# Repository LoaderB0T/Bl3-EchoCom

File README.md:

# Borderlands 3 - Echo Device

This repo contains all the needed files to create your own 3D printed Echo Com from Borderlands 3.
I put lots of images in the repo so the size got quite big, sorry for that 🤷‍♂️.

If you need additional information or have any questions please just open an issue and I will try to answer them 😀.
And please, if you decide to give it a shot and you use my model, please please send me pictures of the result! :) Just open an issue here to show off your amazing work.

## Printing

- I printed all opaque parts with PLA filament with 0.15mm layer height.
- For the electronics version, the inner projector part was printed with "transparent" PETG filament to let the light of the LEDs pass through.
- I Recommend printing more or less everything with full support to make sure all the complex parts get printed properly.
- Removing the supports is quite easy with this model.

## Components for the electronics version

- [4" TFT Display](https://www.waveshare.com/4inch-tft-touch-shield.htm)
  - I really recommend buying exactly this one as the 3D model is designed for exactly this product.
  - It was the only display I found that had the correct size for the EchoCom.
  - You have to remove the pin headers from the backside for it to fit into the model. The required wires then can be re-soldered with a thinner footprint.
- Custom PCB
  - You can find the KiCad project and a finished plot of the PCB in the `pcb` folder.
  - Use a service like [JLCPCB](jlcpcb.com) to have it manufactured or you can of course do it yourself :)
- Electronic Components:
  - 1x Atmega328P-PU
  - 8x Push Button
  - 2x 22pF ceramic capacitors
  - 1x 16MHz Crystal
  - 3x 100nF foil capacitor
  - 1x 10K Ohm resistor
  - 2x Digital RGB LEDs (eg WS2812B) (one or maybe more than two might also work for you)
  - 2x Screw Terminals (optional, you can also solder the power wires)
  - Pin Header (optional, you can also solder the wires, but I recommend the headers!)
    - 2x 3-pin
    - 2x 5-pin
    - 1x 6-pin
- Some sort of power source (I have not yet figured this out)
- Wires (with correct heads depending on your pin headers)

## Code

The code is very, very unfinished!
I recommend [Visual Studio Code](https://code.visualstudio.com/) to edit the code. The code is a [PlatformIO](https://platformio.org/) project, so I recommend the [PlatformIO extension](https://marketplace.visualstudio.com/items?itemName=platformio.platformio-ide) for VSCode.

## Images

|                                                                                                                  |                                                                                                                   |                                                                                                                   |
| :--------------------------------------------------------------------------------------------------------------: | :---------------------------------------------------------------------------------------------------------------: | :---------------------------------------------------------------------------------------------------------------: |
|  |   |   |
|  |   |   |
|  |  |  |

## Progress images

|                                                                                                                                       |                                                                                                                                       |                                                                                                                                       |
| :-----------------------------------------------------------------------------------------------------------------------------------: | :-----------------------------------------------------------------------------------------------------------------------------------: | :-----------------------------------------------------------------------------------------------------------------------------------: |
|  |  |  |
|  |  |  |
|  |  |  |
|  |  |  |
|  |  |  |
|  |  |  |
|  |  |  |
|  |  |  |
|  |  |  |
|  |  |

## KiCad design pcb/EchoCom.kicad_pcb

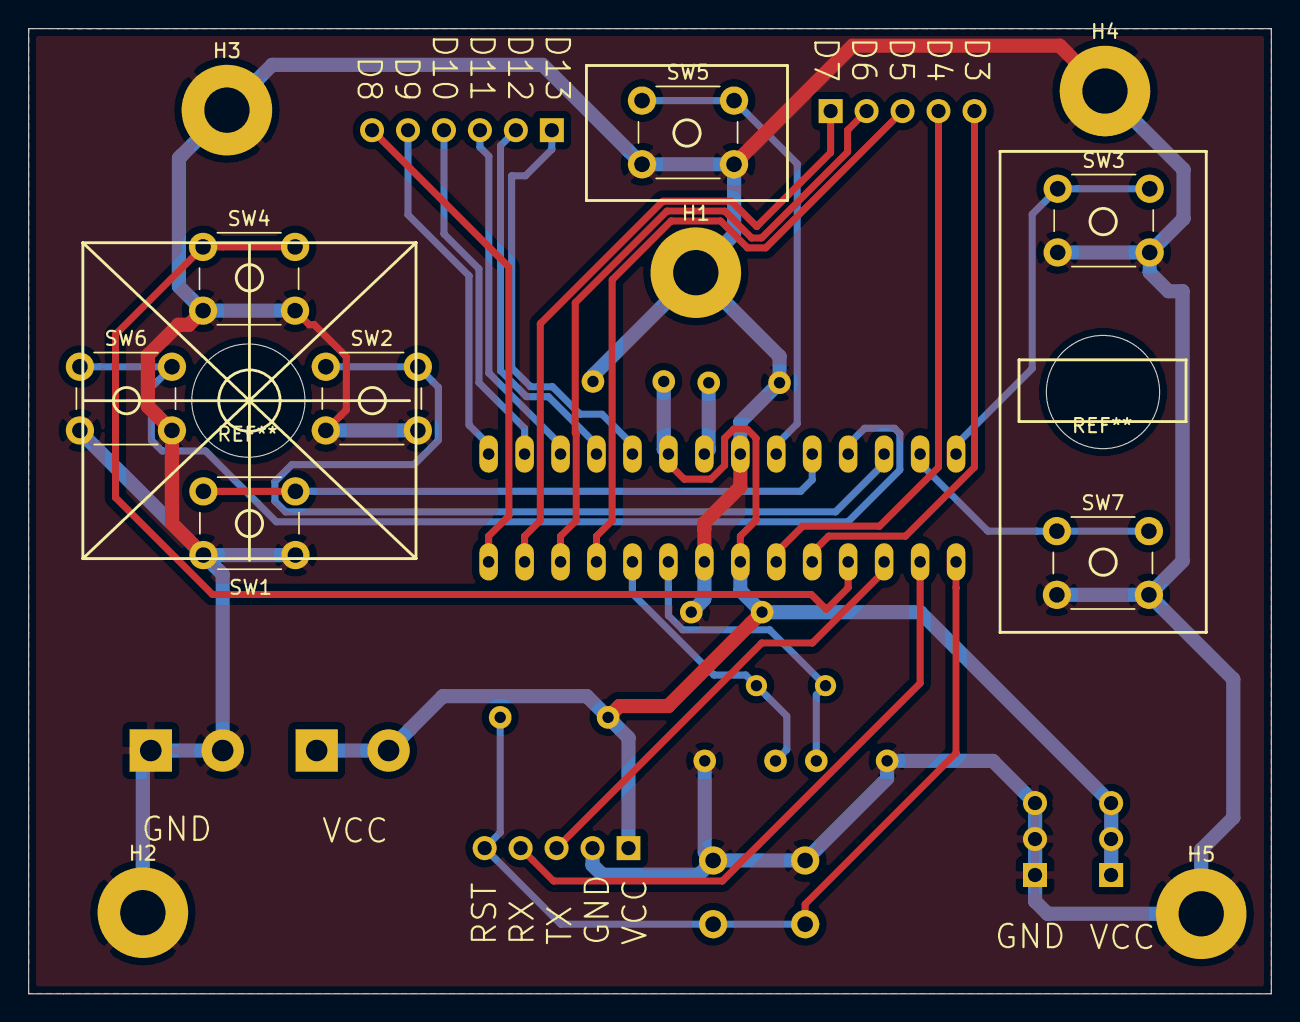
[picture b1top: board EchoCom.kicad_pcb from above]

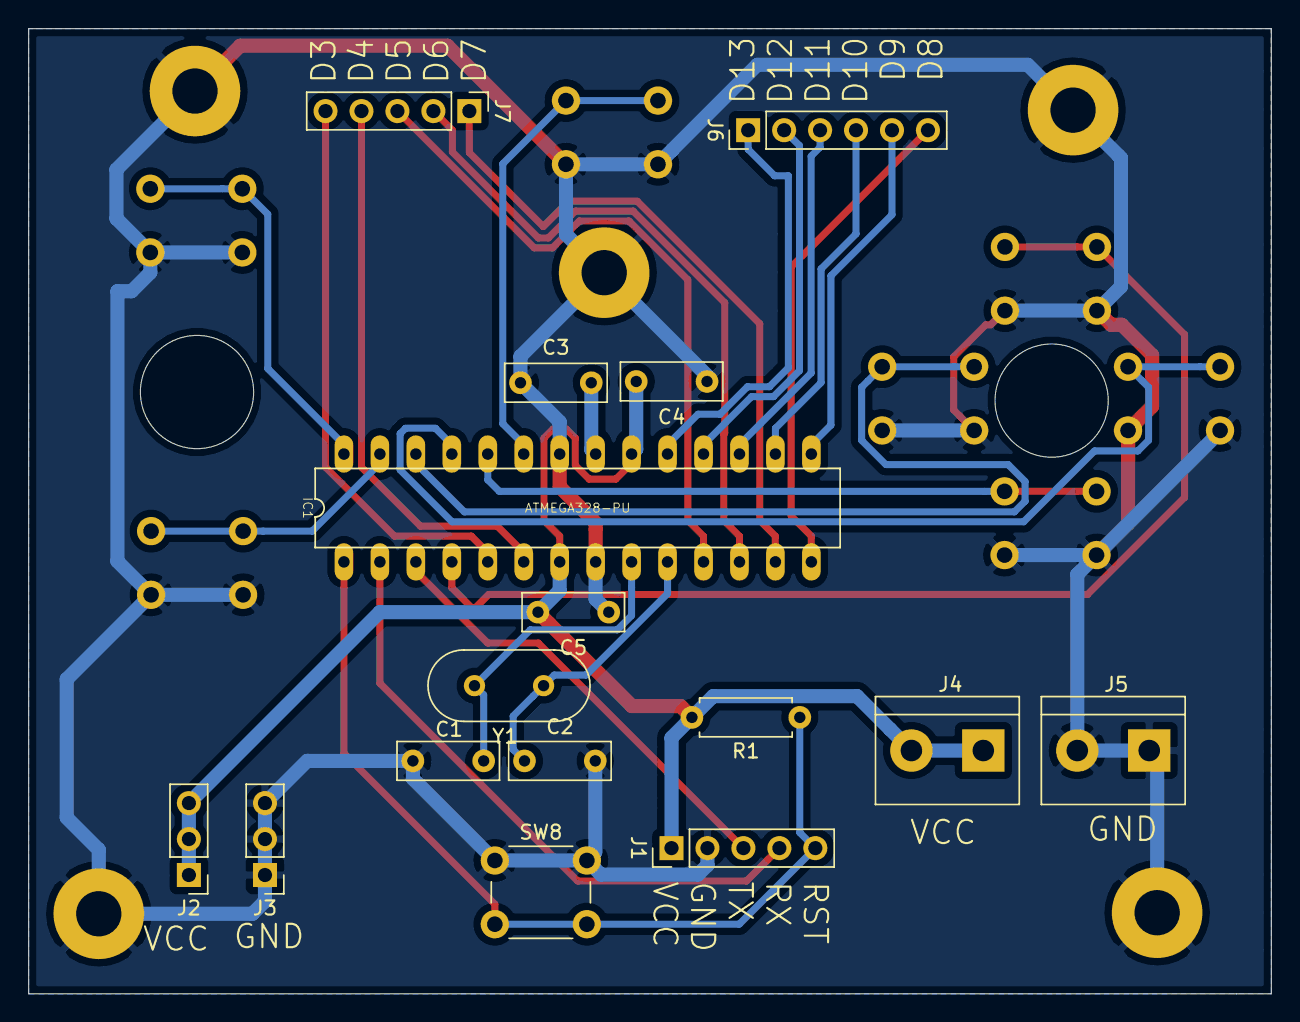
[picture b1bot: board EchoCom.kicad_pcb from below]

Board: 2 copper layers, 87.8 x 68.2 mm, 28 parts (16 on the bottom side), 26 nets.

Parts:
C1, C2, C3, C4, C5: C; C_Rect_L7.0mm_W2.5mm_P5.00mm
H1, H2, H3, H4, H5: MountingHole_Pad; MountingHole_3.2mm_M3_Pad
IC1: ATMEGA328-PU; DIL28
J1: Conn_Programmer; PinHeader_1x05_P2.54mm_Vertical
J2: Conn_VCC (5v); PinHeader_1x03_P2.54mm_Vertical
J3: Conn_GND; PinHeader_1x03_P2.54mm_Vertical
J4: Screw_Terminal_VCC; TerminalBlock_bornier-2_P5.08mm
J5: Screw_Terminal_GND; TerminalBlock_bornier-2_P5.08mm
J6: Conn_01x06_Male; PinHeader_1x06_P2.54mm_Vertical
J7: Conn_01x05_Male; PinHeader_1x05_P2.54mm_Vertical
R1: R; R_Axial_DIN0207_L6.3mm_D2.5mm_P7.62mm_Horizontal
SW1: SW_Cross_Down; SW_PUSH_6mm_H5mm
SW2: SW_Cross_Right; SW_PUSH_6mm_H5mm
SW3: SW_Dual_Up; SW_PUSH_6mm_H5mm
SW4: SW_Cross_Up; SW_PUSH_6mm_H5mm
SW5: SW_Single; SW_PUSH_6mm_H5mm
SW6: SW_Cross_Left; SW_PUSH_6mm_H5mm
SW7: SW_Dual_Down; SW_PUSH_6mm_H5mm
SW8: SW_Reset; SW_PUSH_6mm_H5mm
Y1: Crystal; Crystal_HC49-4H_Vertical

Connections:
unnamed: C1.1, C2.1, C3.1, C4.1, C5.1, H1.1, H2.1, H3.1, H4.1, H5.1, IC1.8, IC1.22, J1.2, J3.1, J3.2, J3.3, J5.1, J5.2, SW1.2, SW2.2, SW3.2, SW4.2, SW5.2, SW6.2, SW7.2, SW8.1
unnamed: C1.2, IC1.9, Y1.2
unnamed: C2.2, IC1.10, Y1.1
unnamed: C3.2, IC1.21
unnamed: C4.2, C5.2, IC1.7, IC1.20, J1.1, J2.1, J2.2, J2.3, J4.1, J4.2, R1.2
unnamed: IC1.1, J1.5, R1.1, SW8.2
unnamed: IC1.2, J1.4
unnamed: IC1.3, J1.3
unnamed: IC1.4, SW4.1
unnamed: IC1.5, J7.5
unnamed: IC1.6, J7.4
unnamed: IC1.11, J7.3
unnamed: IC1.12, J7.2
unnamed: IC1.13, J7.1
unnamed: IC1.14, J6.6
unnamed: IC1.15, J6.5
unnamed: IC1.16, J6.4
unnamed: IC1.17, J6.3
unnamed: IC1.18, J6.2
unnamed: IC1.19, J6.1
unnamed: IC1.23, SW5.1
unnamed: IC1.24, SW1.1
unnamed: IC1.25, SW6.1
unnamed: IC1.26, SW2.1
unnamed: IC1.27, SW7.1
unnamed: IC1.28, SW3.1

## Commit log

2020-08-17 init
2020-08-17 added pcb stuff and started readme
2020-08-18 Rename README to README.md
2020-08-18 added in-progress images
2020-08-18 img changes
2020-08-18 Revert "img changes"
    This reverts commit afa6c2970734dd34bfda38bfac79ff949f215cf8.
2020-08-18 img fixes
2022-09-04 compressed
2022-09-04 readme
